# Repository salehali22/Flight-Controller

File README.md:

<h1 align="center">SAL FC</h1>

<p align="center">
  Open-source flight controller platform built on the STM32H743VIT6
</p>

---

SAL FC is a custom 40.5 x 40.5 mm, six-layer flight controller PCB designed to bridge the gap between compact FPV racing boards and full-size autopilot systems. It supports three open-source firmware stacks (Betaflight, iNAV, and ArduPilot) on a single board with standard 30.5 mm mounting, dual IMUs, and a companion computer interface. Designed as a senior capstone project at Ilia State University, Tbilisi, Georgia.

---

## Table of Contents

- [Features](#features)
- [Hardware Specifications](#hardware-specifications)
- [Pin Mapping](#pin-mapping)
- [Wiring Diagrams](#wiring-diagrams)
- [Getting Started](#getting-started)
  - [Flashing Betaflight](#flashing-betaflight)
  - [Flashing iNAV](#flashing-inav)
  - [Flashing ArduPilot](#flashing-ardupilot)
- [Building from Source](#building-from-source)
- [CLI Backup and Restore](#cli-backup-and-restore)
- [Repository Structure](#repository-structure)
- [License](#license)
- [Credits](#credits)

---

## Features

- Three open-source firmware stacks supported: Betaflight 4.5.1, iNAV 9.0.1, and ArduPilot, compiled from source with custom target definitions
- Dual dissimilar IMUs on separate SPI buses, following Pixhawk FMUv6C redundancy guidelines
- 12 PWM motor/servo outputs on advanced timers (TIM1, TIM8, TIM4) with independent DMA channels per output, eliminating stream contention
- DSHOT150/300/600 protocol support with bidirectional telemetry
- MAVLink v2 companion computer interface over dedicated UART
- CRSF / ExpressLRS receiver input, IRC Tramp VTX control, DJI air unit support
- GPS and magnetometer passthrough on I2C4, CAN bus for DroneCAN peripherals
- USB-C with host and device support, 90 ohm differential impedance routing
- Reverse polarity protection (P-FET) and TVS diode protection on USB and power inputs
- Six-layer PCB with dedicated ground planes, ENIG finish, resin-plugged vias
- JST-SH 1.0 mm connectors on all ports with solder pad fallback
- iNAV SPI6 HAL patch included for ICM42688P detection (see [`Firmware Target Files/iNAV/`](Firmware%20Target%20Files/iNAV/))

---

## Hardware Specifications

<details>
<summary>Click to expand full specifications table</summary>

| Parameter | Value |
|---|---|
| **MCU** | STM32H743VIT6 (Cortex-M7, 480 MHz, 2 MB flash, 1 MB SRAM) |
| **Primary IMU** | TDK ICM42688P (SPI6, up to 32 kHz sampling) |
| **Secondary IMU** | Bosch BMI270 (SPI3, up to 6.4 kHz sampling) |
| **Barometer** | Bosch BMP388 (I2C2) |
| **OSD** | AT7456E (SPI4) |
| **Flash** | Winbond W25Q128JVSIQ, 128 Mbit (SPI1) |
| **CAN transceiver** | SN65HVD230D (ISO 11898) |
| **UARTs** | 7 |
| **SPI buses** | 4 |
| **I2C buses** | 3 |
| **PWM outputs** | 12 (8 motor + 4 servo) |
| **Motor protocol** | DSHOT150 / 300 / 600 |
| **Input voltage** | Up to 6S (25.2 V) |
| **5V rail** | AP63205WU buck converter |
| **9/12V VTX rail** | TPS54302 buck converter |
| **3.3V logic rail** | AP2112K-3.3 LDO |
| **3.3V sensor rail** | AP7343-33W5-7 low-noise LDO (dedicated IMU/baro supply) |
| **USB** | Type-C, host + device, 90 ohm differential routing |
| **Protection** | P-FET reverse polarity (AO3407A), TVS on USB/battery/5V, PTC fuses |
| **PCB** | 6-layer, FR-4, JLC06161H-3313, ENIG finish, resin-plugged vias |
| **Dimensions** | 40.5 x 40.5 mm |
| **Mounting** | 30.5 x 30.5 mm, M3 |
| **Weight (bare board)** | ~8 g |
| **Design tool** | KiCad |
| **Fabrication** | JLCPCB |

</details>

---

## Pin Mapping

### UART Assignments

| UART | Function | Pins (TX / RX) | Protocol |
|---|---|---|---|
| USART1 | Expansion / companion computer | PA9 / PA10 | MAVLink v2 |
| USART2 | VTX | PD5 / PD6 | IRC Tramp |
| USART3 | RC receiver | PD8 / PD9 | CRSF / ELRS |
| UART5 | General telemetry | PB6 / PB12 | User-assigned |
| UART7 | DJI air unit | PE8 / PE7 | MSP |
| UART8 | GPS | PE1 / PE0 | UBX / NMEA |

### SPI Bus Assignments

| SPI | Peripheral | CS | SCK / MISO / MOSI | Interrupt |
|---|---|---|---|---|
| SPI1 | W25Q128 flash | PA4 | PA5 / PA6 / PA7 | -- |
| SPI3 | BMI270 (secondary IMU) | PD3 | PC10 / PC11 / PC12 | PD2 |
| SPI4 | AT7456E OSD | PC13 | PE2 / PE5 / PE6 | -- |
| SPI6 | ICM42688P (primary IMU) | PD7 | PB3 / PB4 / PB5 | PE4 |

### Motor and Servo Outputs

| Output | Timer | Channel | Pin |
|---|---|---|---|
| Motor 1 | TIM1 | CH1 | PE9 |
| Motor 2 | TIM1 | CH2 | PE11 |
| Motor 3 | TIM1 | CH3 | PE13 |
| Motor 4 | TIM1 | CH4 | PE14 |
| Motor 5 | TIM8 | CH1 | PC6 |
| Motor 6 | TIM8 | CH2 | PC7 |
| Motor 7 | TIM8 | CH3 | PC8 |
| Motor 8 | TIM8 | CH4 | PC9 |
| Servo 1 | TIM4 | CH1 | PD12 |
| Servo 2 | TIM4 | CH2 | PD13 |
| Servo 3 | TIM4 | CH3 | PD14 |
| Servo 4 | TIM4 | CH4 | PD15 |

### I2C Bus Assignments

| I2C | Peripheral | Pins (SCL / SDA) |
|---|---|---|
| I2C2 | BMP388 barometer | PB10 / PB11 |
| I2C4 | GPS magnetometer / external | PB8 / PB7 |
| I2C (ext) | Airspeed sensor connector | Exposed on JST-SH |

### CubeMX Pin Map

### Board Layout

---

## Wiring Diagrams

---

## Getting Started

### Flashing Betaflight

**Requirements:** Betaflight Configurator **10.10.0 standalone** (not the web version or the 2026.x alpha, which locks custom boards into CLI-only developer mode).

1. Enter DFU mode: hold the **BOOT** button while connecting USB-C.
2. Open Betaflight Configurator 10.10.0 and navigate to the **Firmware Flasher** tab.
3. Select **Load Firmware [Local]** and choose the SAL FC `.hex` file from [`Firmware Target Files/Betaflight/`](Firmware%20Target%20Files/Betaflight/).
4. Click **Flash Firmware**.
5. After flashing, the board will reboot and appear as a COM port.

> [!NOTE]
> Motor pin assignments (PE9/PE11/PE13/PE14 on TIM1, PC6-PC9 on TIM8) should be defined in `target.h` via `MOTOR1_PIN` through `MOTOR8_PIN`. If your hex was built without these defines, you will need to assign motors manually using the CLI `resource` command after flashing.

### Flashing iNAV

**Requirements:** [STM32CubeProgrammer](https://www.st.com/en/development-tools/stm32cubeprog.html)

1. Enter DFU mode: hold the **BOOT** button while connecting USB-C.
2. Open STM32CubeProgrammer, connect via **USB**, and erase the chip with **Full chip erase**.
3. Load the SAL FC iNAV `.hex` file from [`Firmware Target Files/iNAV/`](Firmware%20Target%20Files/iNAV/) and click **Start Programming**.
4. Disconnect and reconnect USB (without BOOT button). The board should enumerate as a COM port.
5. Open the iNAV Configurator to verify sensor detection.

> [!IMPORTANT]
> iNAV's STM32H743 HAL only enumerates SPI1 through SPI4 by default. The ICM42688P on SPI6 will not be detected without the custom SPI6 patch. The patched firmware hex in this repository already includes the fix. If building from source, apply the patch files in [`Firmware Target Files/iNAV/spi6-patch/`](Firmware%20Target%20Files/iNAV/spi6-patch/) before compiling. See [Building from Source](#building-from-source) for details.

> [!WARNING]
> Do **not** enable GPS in the iNAV Ports tab unless a GPS module is physically connected. Enabling GPS without hardware triggers a HWFAIL arming flag that prevents arming.

### Flashing ArduPilot

**Requirements:** [STM32CubeProgrammer](https://www.st.com/en/development-tools/stm32cubeprog.html), [Mission Planner](https://ardupilot.org/planner/docs/mission-planner-installation.html)

**Step 1 -- Flash the bootloader:**

1. Enter DFU mode: hold the **BOOT** button while connecting USB-C.
2. Open STM32CubeProgrammer, connect via **USB**, and perform a **Full chip erase**.
3. Load `SALFC_bl.bin` from [`Firmware Target Files/ArduPilot/`](Firmware%20Target%20Files/ArduPilot/) and click **Start Programming**.
4. Disconnect USB.

**Step 2 -- Flash the firmware:**

1. Reconnect USB (without BOOT button). The board should enumerate as a COM port.
2. Open Mission Planner and connect to the board.
3. Go to **Setup > Install Firmware > Load custom firmware** and select `arducopter.apj` from [`Firmware Target Files/ArduPilot/`](Firmware%20Target%20Files/ArduPilot/).
4. Wait for the flash to complete and verify telemetry and sensor detection.

**Subsequent updates:**

Once the bootloader is installed, future firmware updates follow Step 2 only.

> [!NOTE]
> The provided firmware is built for quadcopter (ArduCopter). Builds for octocopter and fixed-wing configurations will be available soon.

> [!IMPORTANT]
> The SAL FC uses an 8 MHz oscillator, **not** a passive crystal. The ArduPilot `hwdef.dat` must **not** define `STM32_HSE_BYPASS`. If bypass mode is enabled, the PLL will fail to lock and USB will not enumerate. The target files in this repository are already configured correctly.

---

## Building from Source

<details>
<summary>Betaflight 4.5.1</summary>

```bash
# Ubuntu / WSL2
sudo apt install gcc-arm-none-eabi git make

git clone https://github.com/betaflight/betaflight.git
cd betaflight
git checkout v4.5.1

# Copy SAL FC target files into the source tree
cp -r "/path/to/Firmware Target Files/Betaflight/SALFC" src/main/target/SALFC

make TARGET=SALFC

# Output hex: obj/betaflight_4.5.1_SALFC.hex
```

</details>

<details>
<summary>iNAV 9.0.1 (with SPI6 patch)</summary>

```bash
# Ubuntu / WSL2
sudo apt install gcc-arm-none-eabi git make cmake

git clone https://github.com/iNavFlight/inav.git
cd inav
git checkout v9.0.1

# Copy SAL FC target
cp -r "/path/to/Firmware Target Files/iNAV/SALFC" src/main/target/SALFC

# Apply SPI6 patch (5 files, ~60 lines)
# This extends iNAV's SPI bus abstraction from SPI4 to SPI6
# so the ICM42688P on SPI6 is detected.
git apply "/path/to/Firmware Target Files/iNAV/spi6-patch/inav-spi6.patch"

mkdir build && cd build
cmake ..
make SALFC

# Output hex: build/bin/inav_9.0.1_SALFC.hex
```

The SPI6 patch modifies five files:
- `src/main/drivers/bus_spi.h` -- extends `SPIDevice` enum to include `SPIDEV_5` and `SPIDEV_6`
- `src/main/drivers/bus.h` -- adds `BUS_SPI5`, `BUS_SPI6` defines and `busIndex_e` entries
- `src/main/drivers/bus_spi_stm32h7xx.h` -- adds GPIO AF8 mappings for SPI6 pins (PB3/PB4/PB5)
- `src/main/drivers/bus_spi_hal_ll.c` -- adds SPI6 hardware map entry (APB4 clock, pin assignment)
- `target/SALFC/target.h` -- enables `USE_SPI_DEVICE_6` and registers ICM42688P on SPI6

SPI6 operates in polling mode (not DMA), so BDMA/SRAM4 constraints do not apply.

</details>

<details>
<summary>ArduPilot</summary>

```bash
# Ubuntu / WSL2
git clone --recurse-submodules https://github.com/ArduPilot/ardupilot.git
cd ardupilot
Tools/environment_install/install-prereqs-ubuntu.sh -y
. ~/.profile

# Copy SAL FC hardware definition
cp -r "/path/to/Firmware Target Files/ArduPilot/SALFC" libraries/AP_HAL_ChibiOS/hwdef/SALFC

./waf configure --board SALFC
./waf copter

# Output: build/SALFC/bin/arducopter_with_bl.hex
```

> [!NOTE]
> Do not define `STM32_HSE_BYPASS` in `hwdef.dat`. The board uses an 8 MHz oscillator.

</details>

---

## CLI Backup and Restore

All three firmware stacks support CLI-based configuration backup.

**Betaflight / iNAV:**

```bash
# In the CLI tab of the Configurator:
diff all
```

Copy the entire output and save it to a text file. To restore on a freshly flashed board, paste the contents into the CLI tab and type `save`.

**ArduPilot:**

Use Mission Planner: **Config > Full Parameter List > Save to file** / **Load from file**.

---

## Repository Structure

```
Flight-Controller/
├── 3D Files/                       # Fusion 360 / STEP files for frame and mounts
├── Firmware Target Files/          # Custom target definitions and compiled hex files
│   ├── Betaflight/                 #   Betaflight 4.5.1 target and hex
│   ├── iNAV/                       #   iNAV 9.0.1 target, hex, and SPI6 patch
│   └── ArduPilot/                  #   ArduPilot hwdef and hex
├── Renders and Images/             # PCB renders, photos, wiring diagrams, CubeMX
├── Website/                        # Project landing page
├── firmware/
│   └── Flight_Controller_h7/      # Firmware build workspace
├── recordings/                     # Test recordings and data
├── tools/                          # Build and utility scripts
├── LICENSE                         # CERN-OHL-S-2.0
└── README.md
```

---

## Hardware Files Access

The KiCad project, Gerbers, BOM, pick-and-place files, and 3D models are no longer hosted in this public repository. They have been moved to a private repository ahead of the v2 commercial release.

Developers, researchers, or hobbyists genuinely interested in the hardware design are welcome to reach out. We are happy to share access on a case-by-case basis for legitimate technical, academic, or collaborative purposes.

**Contact:**

| Name | Email | LinkedIn |
|---|---|---|
| Saleh Alhomeidy | salehalhomeidy@gmail.com | [linkedin.com/in/salehalhomeidy](https://www.linkedin.com/in/salehalhomeidy/) |
| Akaki Gvelesiani | akaki.g@hotmail.com | [linkedin.com/in/akaki-gvelesiani-631b27300/](https://www.linkedin.com/in/akaki-gvelesiani-631b27300//) |
| Levani Kazaishvili | Levanikazaishvili@gmail.com |  [linkedin.com/in/levan-kazaishvili-665139289/](https://www.linkedin.com/in/levan-kazaishvili-665139289/) |

Please include a brief description of your interest and intended use when reaching out.

---

## License

This project is licensed under the [CERN Open Hardware Licence Version 2 -- Strongly Reciprocal (CERN-OHL-S-2.0)](LICENSE).

You are free to study, modify, manufacture, and distribute this hardware design under the terms of the license.

---

## Credits

| Name | Role | GitHub |
|---|---|---|
| Saleh Alhomeidy | Project lead, PCB design, firmware porting | [@salehali22](https://github.com/salehali22) |
| Akaki Gvelesiani | Mechanical/technical lead, propulsion testing, sensor fusion | [@kaki04](https://github.com/kaki04) |
| Levani Kazaishvili | Schematic capture, soldering, hardware verification | [@levvans](https://github.com/levvans) |

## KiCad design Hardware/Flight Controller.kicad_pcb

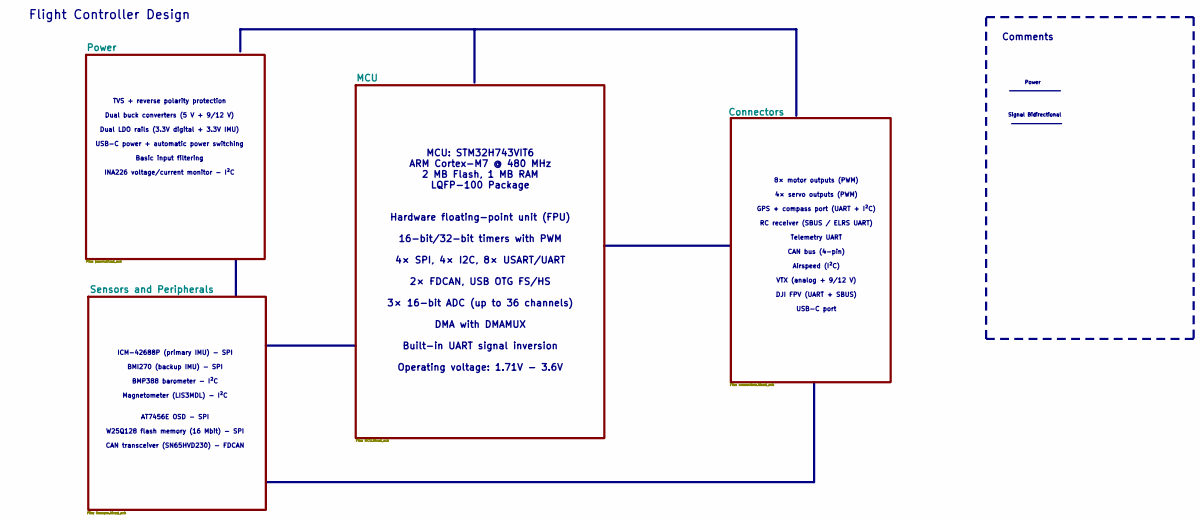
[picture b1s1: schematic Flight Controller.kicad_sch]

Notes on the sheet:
Flight Controller Design
ICM-42688P (primary IMU) - SPI BMI270 (backup IMU) - SPI BMP388 barometer - I²C Magnetometer (LIS3MDL) - I²C AT7456E OSD - SPI W25Q128 flash memory (16 Mbit) - SPI CAN transceiver (SN65HVD230) - FDCAN
Signal Bidirectional
8× motor outputs (PWM) 4× servo outputs (PWM) GPS + compass port (UART + I²C) RC receiver (SBUS / ELRS UART) Telemetry UART CAN bus (4-pin) Airspeed (I²C) VTX (analog + 9/12 V) DJI FPV (UART + SBUS) USB-C port
Comments
TVS + reverse polarity protection Dual buck converters (5 V + 9/12 V) Dual LDO rails (3.3V digital + 3.3V IMU) USB-C power + automatic power switching Basic input filtering INA226 voltage/current monitor - I²C
MCU: STM32H743VIT6 ARM Cortex-M7 @ 480 MHz 2 MB Flash, 1 MB RAM LQFP-100 Package Hardware floating-point unit (FPU) 16-bit/32-bit timers with PWM 4× SPI, 4× I2C, 8× USART/UART 2× FDCAN, USB OTG FS/HS 3× 16-bit ADC (up to 36 channels) DMA with DMAMUX Built-in UART signal inversion Operating voltage: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
Power

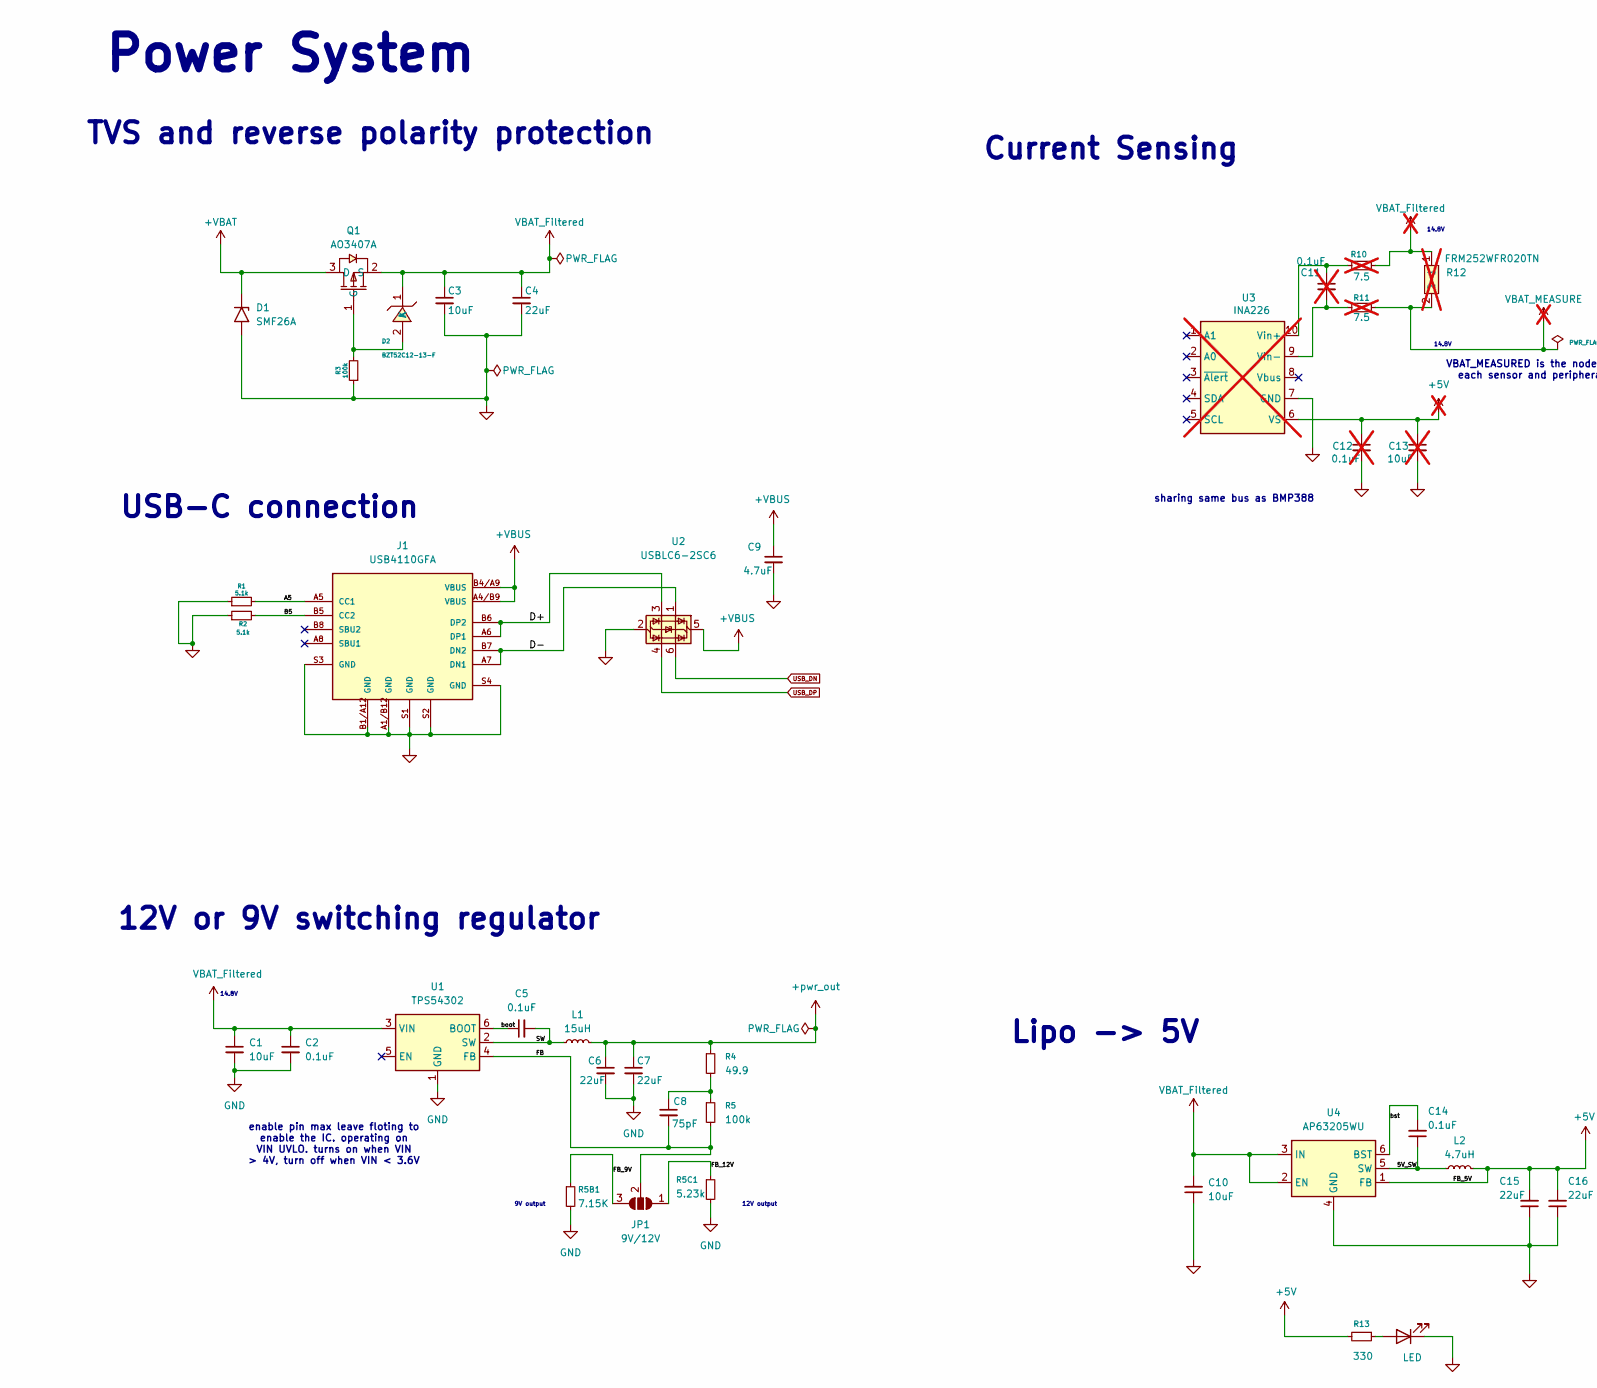
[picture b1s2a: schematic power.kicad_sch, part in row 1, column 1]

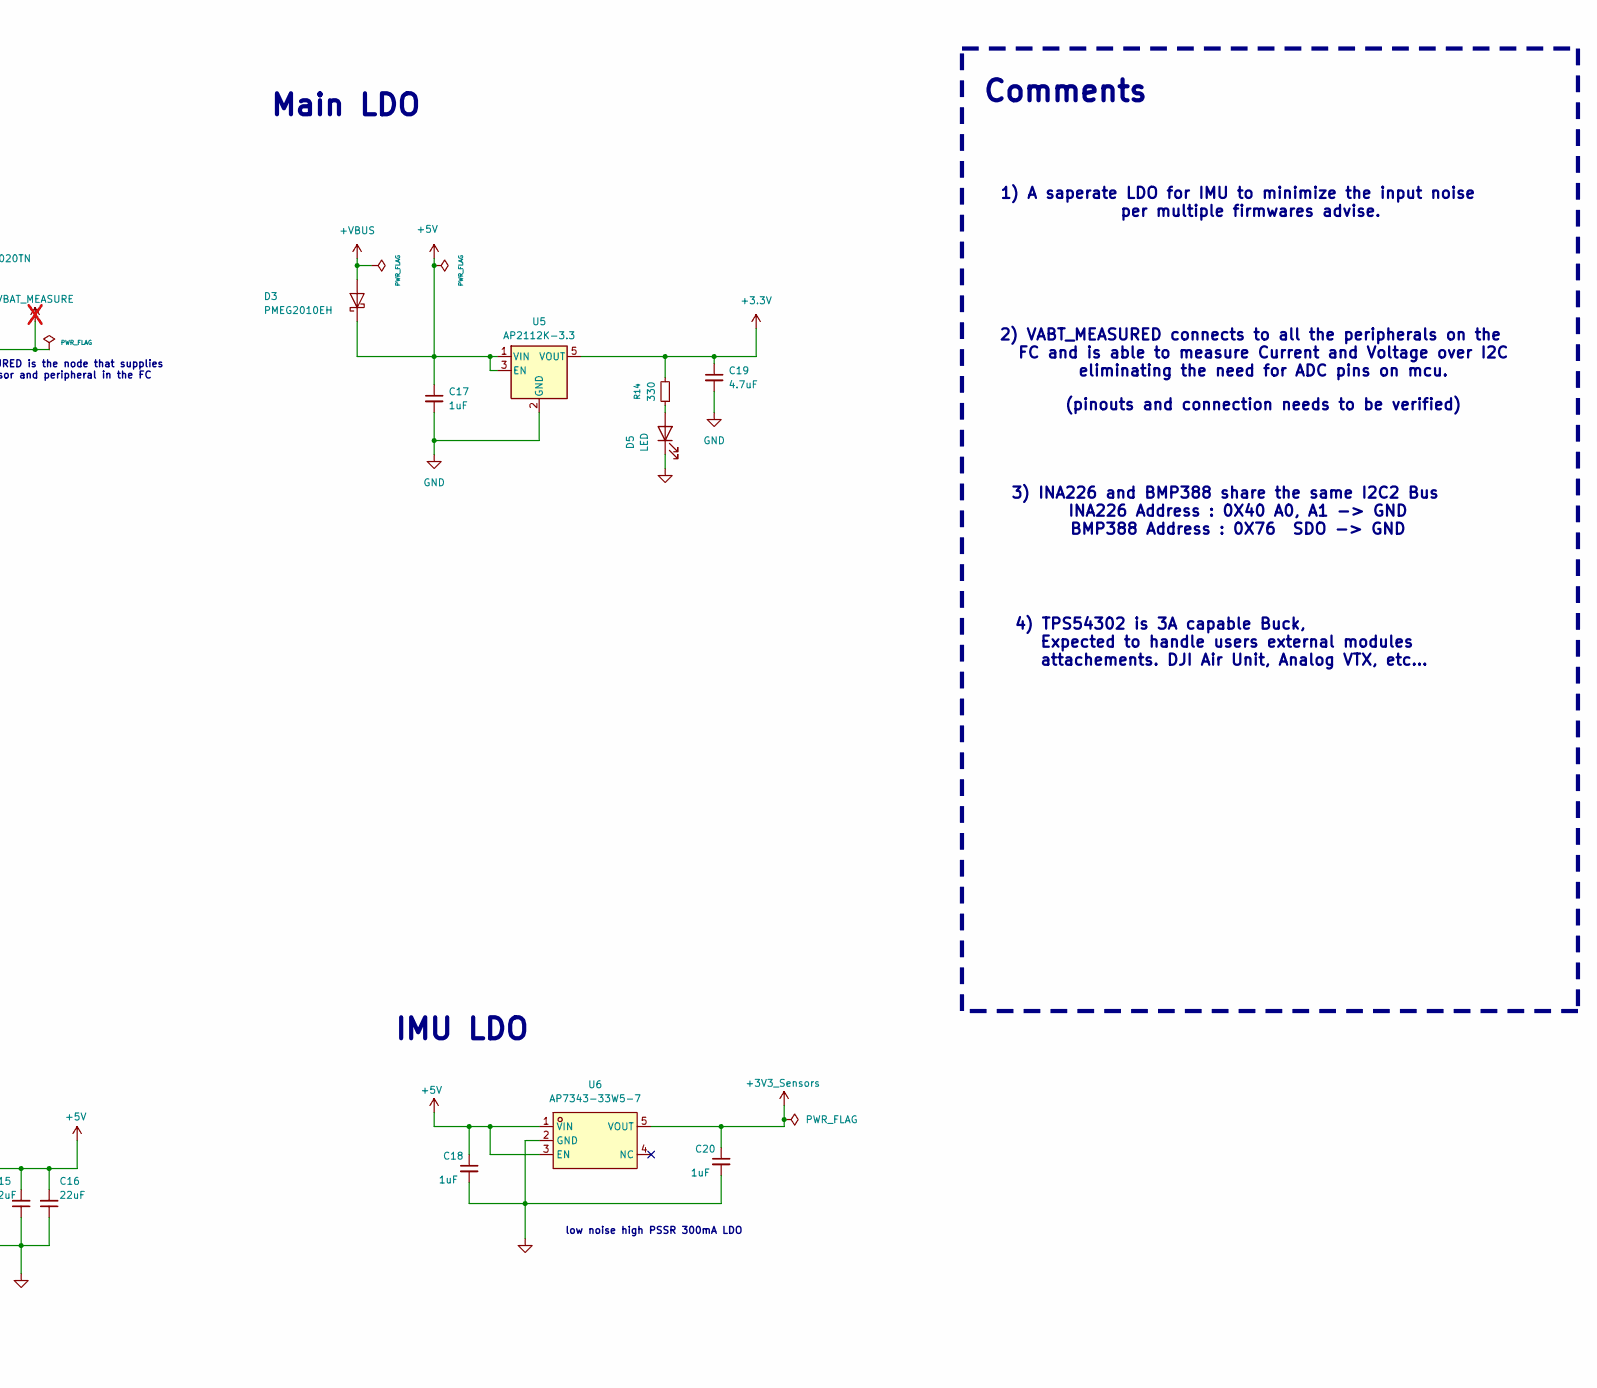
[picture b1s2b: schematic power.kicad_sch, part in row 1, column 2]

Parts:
C1, C3, C10: 10uF; C_0603_1608Metric
C2, C5: 0.1uF; C_0402_1005Metric
C4: 22uF; C_0805_2012Metric
C6, C7, C15, C16: 22uF; C_0603_1608Metric
C8: 75pF; C_0402_1005Metric
C9: 4.7uF; C_0402_1005Metric
C11, C12: 0.1uF; C_0603_1608Metric; not fitted
C13: 10uF; C_0805_2012Metric; not fitted
C14: 0.1uF; C_0603_1608Metric
C17, C18, C20: 1uF; C_0603_1608Metric
C19: 4.7uF; C_0603_1608Metric
D1: SMF26A; D_SMF
D2: BZT52C12-13-F; (zener)SOD-123F_L2.8-W1.8-LS3.7-RD; LCSC Part C177013
D3: PMEG2010EH; D_SOD-123F
D4, D5: LED; LED_0805_2012Metric
J1: USB4110GFA; GCT_USB4110GFA
JP1: 9V/12V; SolderJumper-3_P1.3mm_Open_RoundedPad1.0x1.5mm_NumberLabels
L1: 15uH; IND-SMD_L5.4-W5.2
L2: 4.7uH; IND-SMD_L4.4-W4.2
Q1: AO3407A; LCSC Part C15155
R1, R2: 5.1k; R_0402_1005Metric
R3, R5: 100k; R_0402_1005Metric
R4: 49.9; R_0402_1005Metric
R5B1: 7.15K; R_0402_1005Metric
R5C1: 5.23k; R_0402_1005Metric
R10, R11: 7.5; R_0402_1005Metric; not fitted
R12: FRM252WFR020TN; R2512; LCSC Part C7420049; not fitted
R13, R14: 330; R_0402_1005Metric
U1: TPS54302; SOT-23-6
U2: USBLC6-2SC6; SOT-23-6
U3: INA226; VSSOP-10_3x3mm_P0.5mm; not fitted
U4: AP63205WU; TSOT-23-6
U5: AP2112K-3.3; SOT-23-5
U6: AP7343-33W5-7; (AP7343 )SOT-25_L3.0-W1.6-P0.95-LS2.8-BL; LCSC Part C460383

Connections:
+3.3V: C19.1, R14.2, U5.5 (VOUT); also elsewhere on the board
+3V3_Sensors: C20.1, U6.5 (VOUT); also elsewhere on the board
+5V: C12.1, C13.1, C15.2, C16.2, C17.1, C18.1, D3.1 (K), L2.2, R13.2, U3.6 (VS), U4.1 (FB), U5.1 (VIN), U5.3 (EN), U6.1 (VIN), U6.3 (EN); also elsewhere on the board
+VBAT: D1.1 (A1), Q1.3 (D); also elsewhere on the board
+VBUS: C9.1, D3.2 (A), J1.A4/B9 (VBUS), J1.B4/A9 (VBUS), U2.5 (VBUS)
+pwr_out: C6.1, C7.1, L1.2, R4.1; also elsewhere on the board
/Power/5V_SW: C14.1, L2.1, U4.5 (SW)
/Power/A5: J1.A5 (CC1), R1.2
/Power/B5: J1.B5 (CC2), R2.2
/Power/D+: J1.A6 (DP1), J1.B6 (DP2), U2.3 (I/O2)
/Power/D-: J1.A7 (DN1), J1.B7 (DN2), U2.1 (I/O1)
/Power/FB: C8.2, JP1.2 (C), R5.2, U1.4 (FB)
/Power/FB_9V: JP1.3 (B), R5B1.1
/Power/FB_12V: JP1.1 (A), R5C1.1
/Power/SW: C5.2, L1.1, U1.2 (SW)
/Power/boot: C5.1, U1.6 (BOOT)
/Power/bst: C14.2, U4.6 (BST)
GND: C1.2, C2.2, C3.2, C4.2, C6.2, C7.2, C9.2, C10.1, C12.2, C13.2, C15.1, C16.1, C17.2, C18.2, C19.2, C20.2, D1.2 (A2), D4.1 (K), D5.1 (K), J1.A1/B12 (GND), J1.B1/A12 (GND), J1.S1 (GND), J1.S2 (GND), J1.S3 (GND), J1.S4 (GND), R1.1, R2.1, R3.1, R5B1.2, R5C1.2, U1.1 (GND), U2.2 (GND), U3.7 (GND), U4.4 (GND), U5.2 (GND), U6.2 (GND); also elsewhere on the board
unnamed: C8.1, R4.2, R5.1
unnamed: C11.1, R10.1, U3.10 (Vin+)
unnamed: C11.2, R11.1, U3.9 (Vin-)
unnamed: D2.2 (A), Q1.1 (G), R3.2
unnamed: D4.2 (A), R13.1
unnamed: D5.2 (A), R14.1
unnamed: R11.2, R12.2
USB_DN: U2.6 (I/O1); also elsewhere on the board
USB_DP: U2.4 (I/O2); also elsewhere on the board
VBAT_Filtered: C1.1, C2.1, C3.1, C4.1, C10.2, D2.1 (K), Q1.2 (S), R10.2, R12.1, U1.3 (VIN), U4.2 (EN), U4.3 (IN)

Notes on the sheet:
Lipo -> 5V
Power System
2) VABT_MEASURED connects to all the peripherals on the FC and is able to measure Current and Voltage over I2C eliminating the need for ADC pins on mcu.
low noise high PSSR 300mA LDO
(pinouts and connection needs to be verified)
VBAT_MEASURED is the node that supplies each sensor and peripheral in the FC
9V output
12V output
IMU LDO
TVS and reverse polarity protection
4) TPS54302 is 3A capable Buck, Expected to handle users external modules attachements. DJI Air Unit, Analog VTX, etc...
sharing same bus as BMP388
Comments
3) INA226 and BMP388 share the same I2C2 Bus INA226 Address : 0X40 A0, A1 -> GND BMP388 Address : 0X76 SDO -> GND
14.8V
Current Sensing
12V or 9V switching regulator
USB-C connection
1) A saperate LDO for IMU to minimize the input noise per multiple firmwares advise.
Main LDO
enable pin max leave floting to enable the IC. operating on VIN UVLO. turns on when VIN > 4V, turn off when VIN < 3.6V
